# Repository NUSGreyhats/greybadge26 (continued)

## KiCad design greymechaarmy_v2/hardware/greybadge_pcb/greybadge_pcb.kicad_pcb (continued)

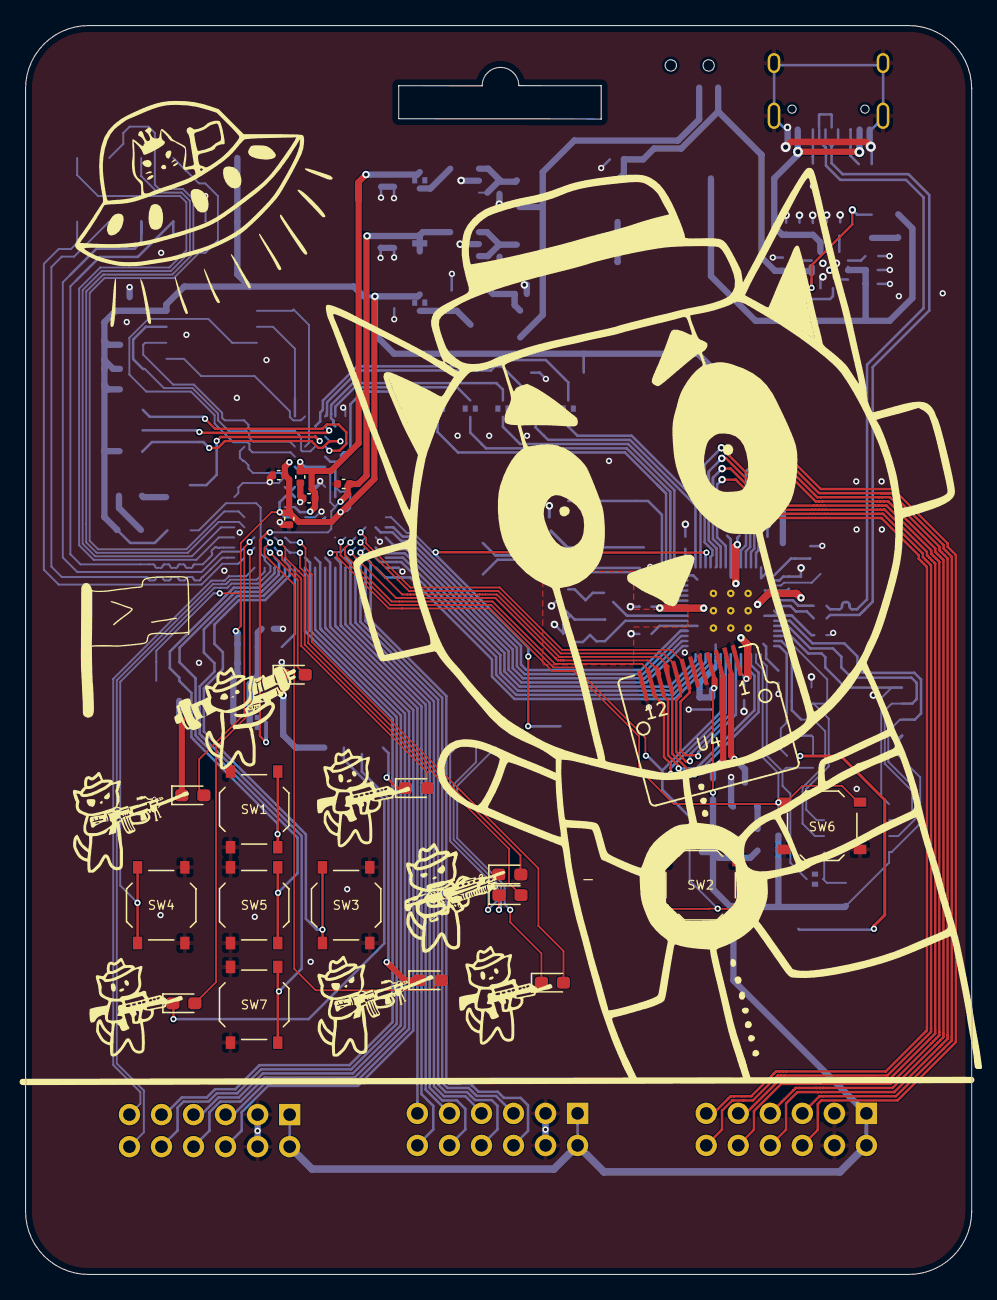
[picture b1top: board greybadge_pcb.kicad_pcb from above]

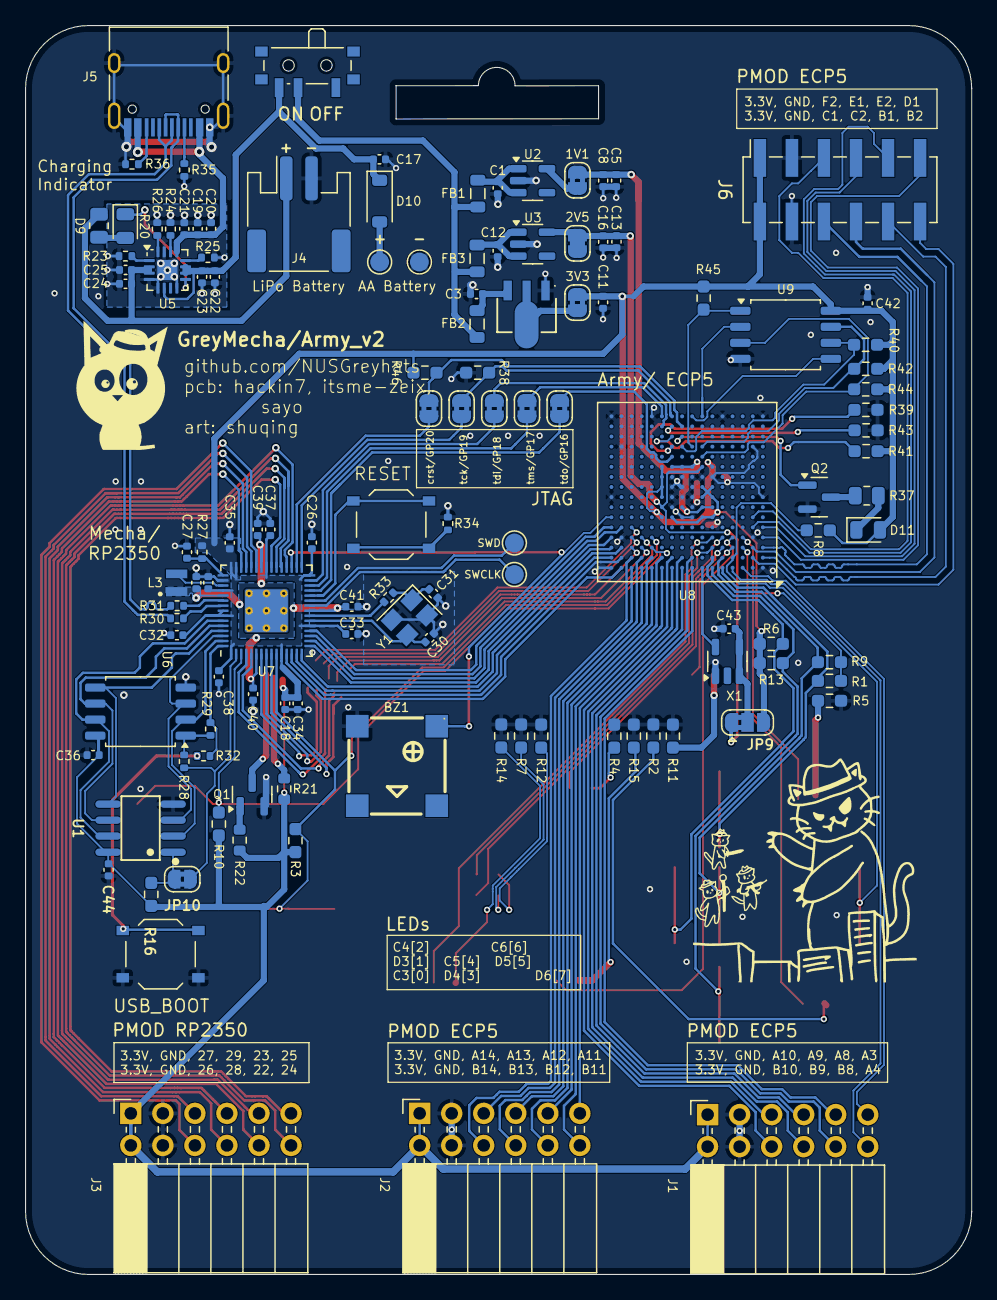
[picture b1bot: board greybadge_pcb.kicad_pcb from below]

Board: 2 copper layers, 75.0 x 99.0 mm, 144 parts (124 on the bottom side), 142 nets.

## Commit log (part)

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2026-02-27 feat: base greymechaarmy version
2026-03-02 fix: spi flash pinout
2026-03-09 feat: PSRAM Schematic addition
2026-03-09 feat: greymecha psram addition in PCB
2026-03-26 flash rerouting
2026-03-26 feat: reroute flash for better efficiency
2026-04-02 feat: update jlcpcb header component + label
2026-04-03 refactor: move jtag and fpga flash
2026-04-03 fix: resolve 1 DRC warning
2026-04-07 feat: add additional pmod header with differential lines
2026-04-10 fix: drc
2026-04-10 feat: fix BOM
2026-04-10 feat: clean up silkscreen
2026-05-26 feat: v2 base firmware
2026-05-27 feat: past solutions
2026-05-27 whatever cursor opus 4.7 got on clanking
2026-05-27 huge detour
2026-05-27 feat: detour lmao
2026-06-07 feat: improve art
2026-06-11 feat: change from via in pad to via out of pad
2026-06-23 firmware update for greyflag
2026-06-23 readme update
2026-06-23 feat: cleanup
2026-06-23 feat: fast secure memory
2026-06-23 feat: add watchdog chall to dist
2026-06-23 feat: cleanup and moving
2026-06-23 feat: challenge dev
2026-06-24 feat: base
2026-06-24 feat: bitstream & compilation
2026-06-24 feat: solve optimal 1
2026-06-24 feat: store optimal
2026-06-24 feat: solve optimal 6 - assembly byte operations
2026-06-24 feat: sample solutions
2026-06-24 feat: naive solve fails
2026-06-24 feat: solution
2026-06-24 participant joiner and organiser commissioner working, left blaster
2026-06-24 feat: filesystem update
2026-06-24 feat: koth plugin
2026-06-24 feat: ctfd plugin updates
2026-06-24 feat: watchdog_koth_api
2026-06-24 feat: api
2026-06-26 finished up entire firmware for participants and organizer, ready for mass flashing
2026-06-26 mass burner file added, 100% ready
2026-06-26 Add Snake badge app
2026-06-27 stripped decrpyt solve
2026-06-27 feat: watchdog_koth_oled viz
2026-06-27 feat: watchdog oled works, easy visualisation
2026-06-27 feat: unfast_secure_memory
2026-06-27 feat: new test
2026-06-28 feat: stuff
